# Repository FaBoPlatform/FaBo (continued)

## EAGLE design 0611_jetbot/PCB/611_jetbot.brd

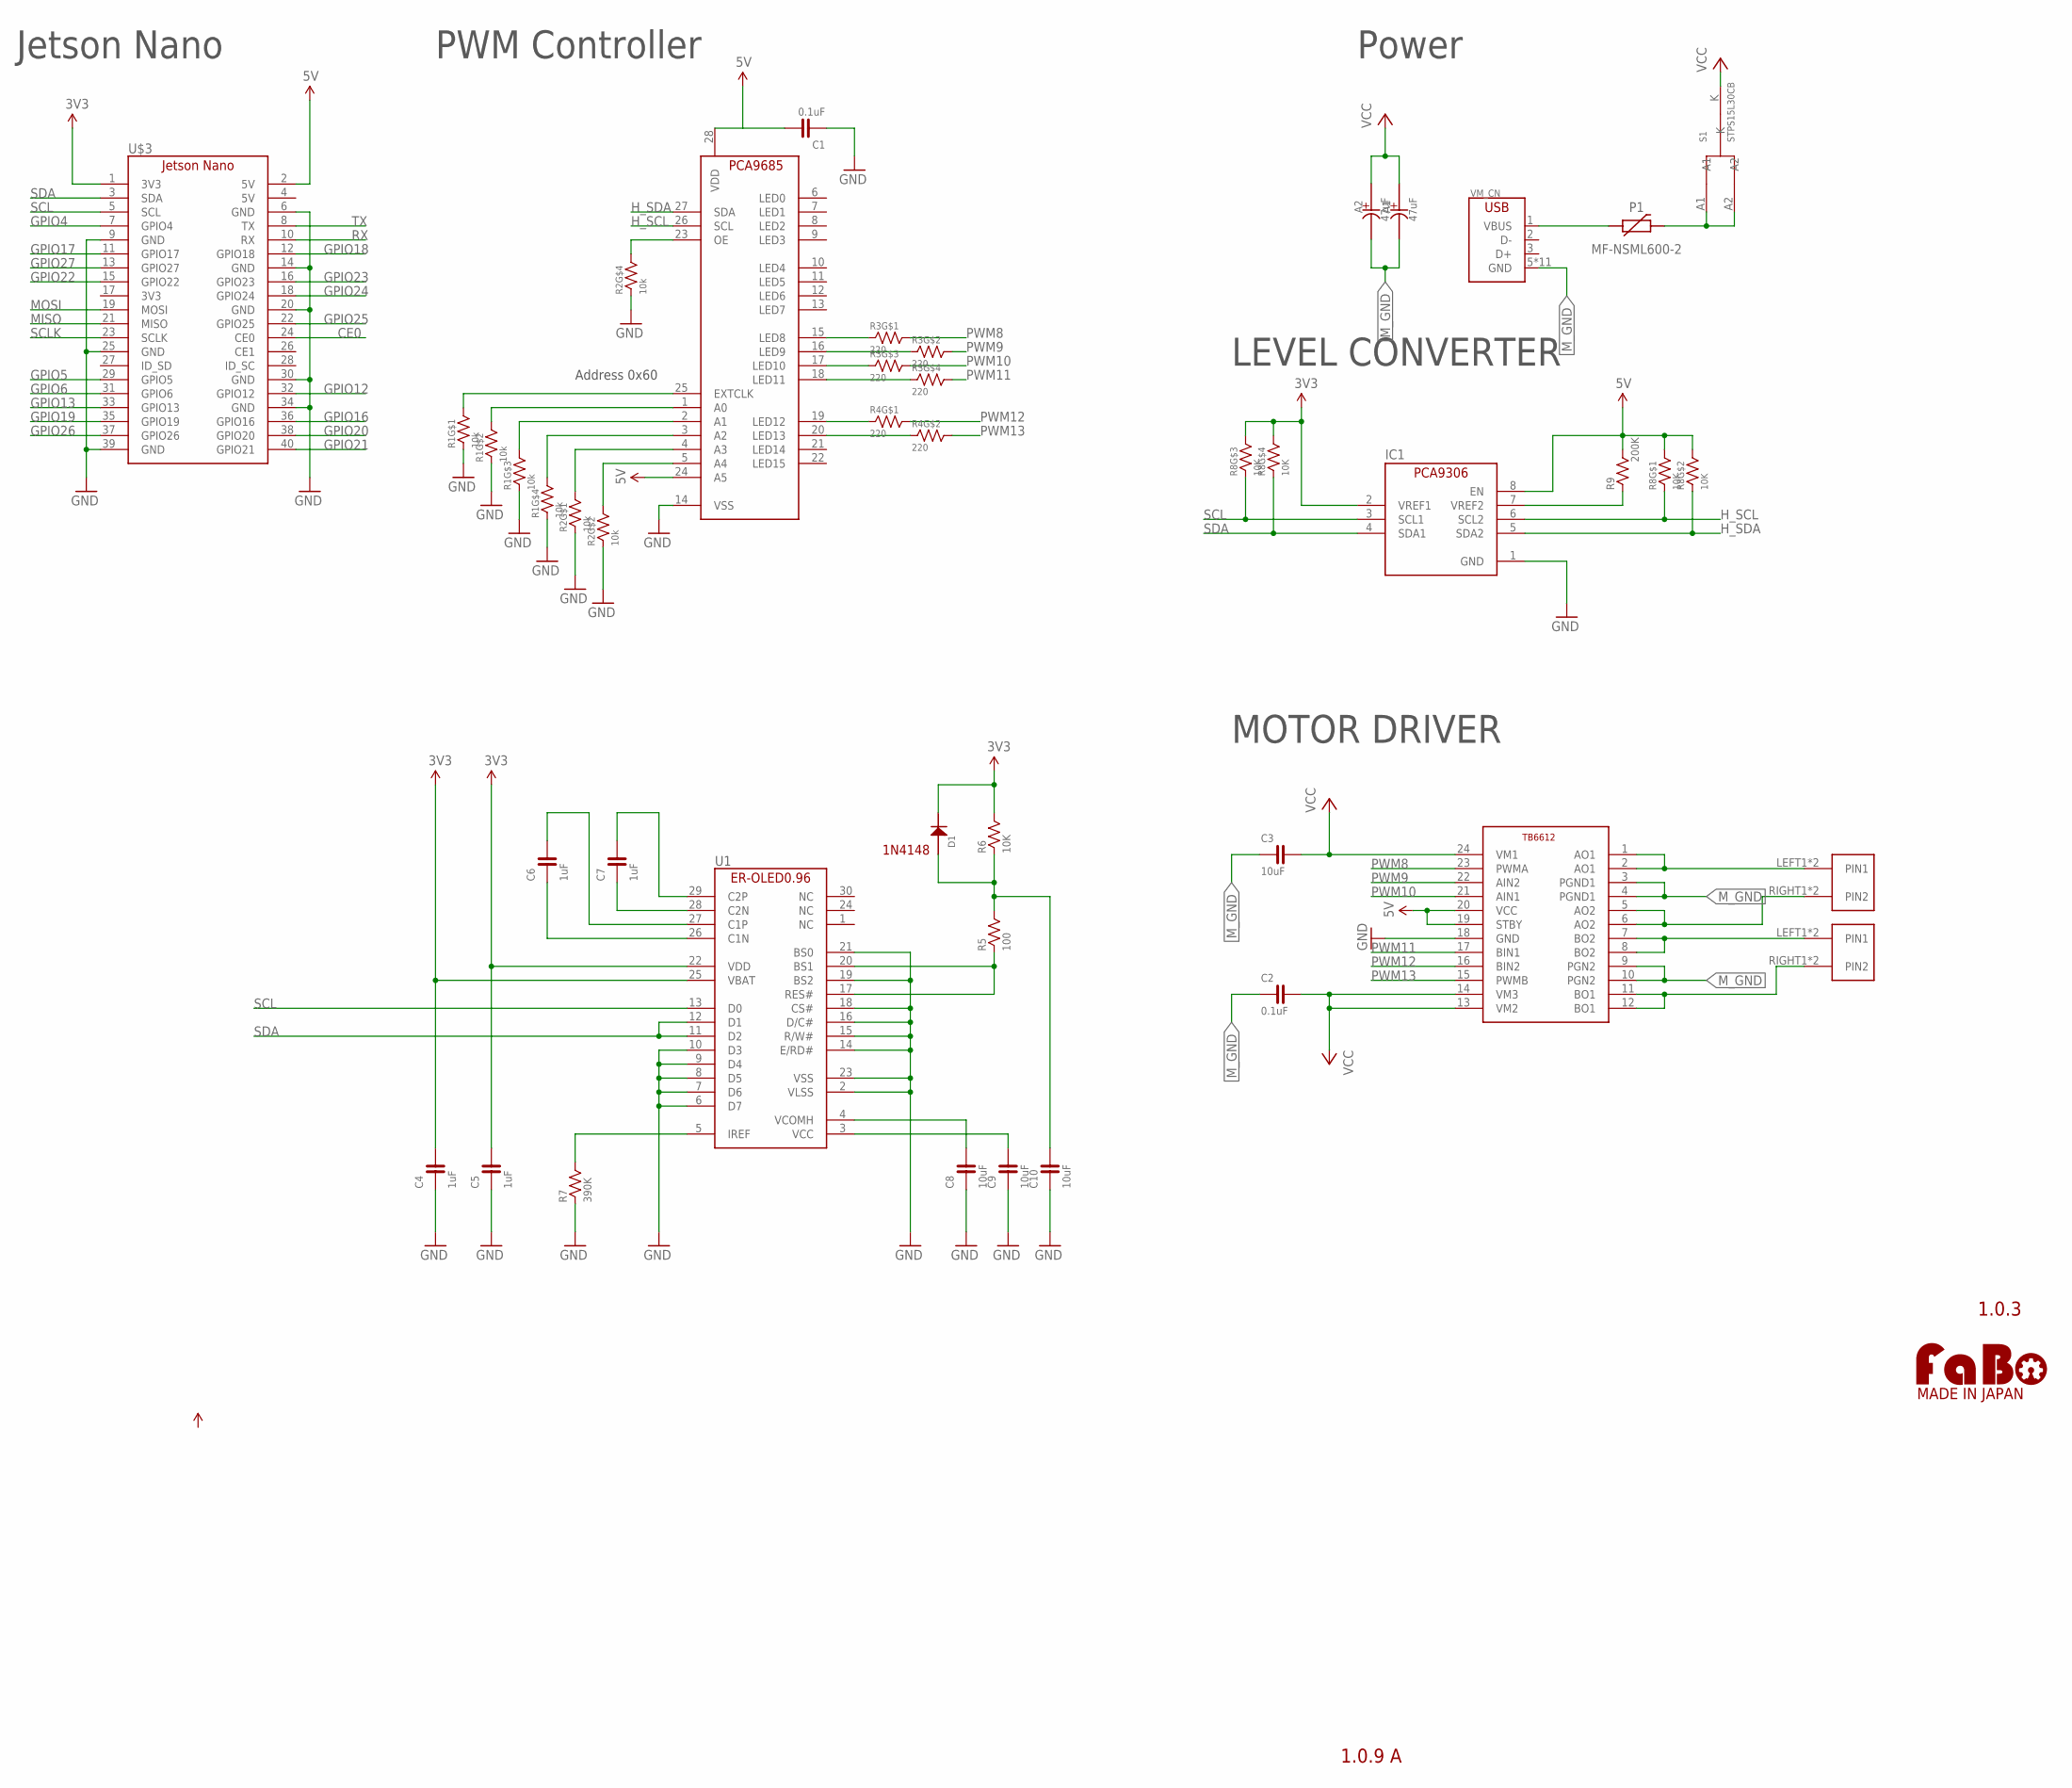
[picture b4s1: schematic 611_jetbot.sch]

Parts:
A1, A2: 47uF; D60
C1, C2: 0.1uF; 0603
C3: 10uF; 0603
C4, C5, C6, C7: 1uF; 0603-BOTTOM
C8, C9, C10: 10uF; 0603-BOTTOM
D1: 1N4148; 1N4148W
IC1: PCA9306_SSOP; 8PIN-SSOP
P1: MF-NSML600-2; 1206
R1, R2: 10k; EXBV8V
R3, R4: 220; EXBV8V
R5: 100; 0603-BOTTOM
R6: 10K; 0603-BOTTOM
R7: 390K; 0603-BOTTOM
R8: 10K; EXBV8V
R9: 200K; 0603
S1: STPS15L30CB; STPS15L30C
U1: ER-OLED0.96-1ER-CON30HT-1; ER-CON30HT-1
U$3: JETSON_NANO
U$5: TB6612
U$6, U$8: ML-1400-S1
U$9: PCA9685
U$14: LOGO_FABO-M; LOGO_FABO_MS
VM_CN: USB-ZX62D; ZX62D-B-5PA8

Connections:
3V3: C4.2, D1.CATHODE, IC1.2 (VREF1), R6.2, R8.5 (2), R8.6 (2), U1.25 (VBAT), U$3.1 (3V3), U$3.17 (3V3)
5V: C1.2, IC1.8 (EN), R8.7 (2), R8.8 (2), R9.2, U$3.2 (5V), U$5.19 (STBY), U$5.20 (VCC), U$9.24 (A5), U$9.28 (VDD)
CE0: U$3.24 (CE0)
GND: C1.1, C4.1, C5.1, C8.1, C9.1, C10.1, IC1.1 (GND), R1.1, R1.2 (1), R1.3 (1), R1.4 (1), R2.1, R2.2 (1), R2.4 (1), R7.1, U1.2 (VLSS), U1.6 (D7), U1.7 (D6), U1.8 (D5), U1.9 (D4), U1.10 (D3), U1.14 (E/RD#), U1.15 (R/W#), U1.16 (D/C#), U1.18 (CS#), U1.19 (BS2), U1.21 (BS0), U1.23 (VSS), U$3.6 (GND), U$3.9 (GND), U$3.14 (GND), U$3.20 (GND), U$3.25 (GND), U$3.30 (GND), U$3.34 (GND), U$3.39 (GND), U$5.18 (GND), U$9.14 (VSS)
GPIO4: U$3.7 (GPIO4)
GPIO5: U$3.29 (GPIO5)
GPIO6: U$3.31 (GPIO6)
GPIO12: U$3.32 (GPIO12)
GPIO13: U$3.33 (GPIO13)
GPIO16: U$3.36 (GPIO16)
GPIO17: U$3.11 (GPIO17)
GPIO18: U$3.12 (GPIO18)
GPIO19: U$3.35 (GPIO19)
GPIO20: U$3.38 (GPIO20)
GPIO21: U$3.40 (GPIO21)
GPIO22: U$3.15 (GPIO22)
GPIO23: U$3.16 (GPIO23)
GPIO24: U$3.18 (GPIO24)
GPIO25: U$3.22 (GPIO25)
GPIO26: U$3.37 (GPIO26)
GPIO27: U$3.13 (GPIO27)
H_SCL: IC1.6 (SCL2), R8.1, U$9.26 (SCL)
H_SDA: IC1.5 (SDA2), R8.2 (1), U$9.27 (SDA)
MISO: U$3.21 (MISO)
MOSI: U$3.19 (MOSI)
M_GND: A1.MINUS (-), A2.MINUS (-), C2.1, C3.1, U$5.3 (PGND1), U$5.4 (PGND1), U$5.9 (PGN2), U$5.10 (PGN2), VM_CN.5 (GND), VM_CN.B1 (GND), VM_CN.B2 (GND), VM_CN.B3 (GND), VM_CN.B4 (GND), VM_CN.T1 (GND), VM_CN.T2 (GND), VM_CN.T3 (GND), VM_CN.T4 (GND), VM_CN.T5 (GND), VM_CN.T6 (GND)
unnamed: R3.1, U$9.15 (LED8)
unnamed: R3.2 (1), U$9.16 (LED9)
unnamed: R3.3 (1), U$9.17 (LED10)
unnamed: R3.4 (1), U$9.18 (LED11)
unnamed: R4.1, U$9.19 (LED12)
unnamed: R2.5 (2), U$9.23 (OE)
unnamed: R1.8 (2), U$9.25 (EXTCLK)
unnamed: R1.7 (2), U$9.1 (A0)
unnamed: R1.6 (2), U$9.2 (A1)
unnamed: R1.5 (2), U$9.3 (A2)
unnamed: R2.8 (2), U$9.4 (A3)
unnamed: R2.7 (2), U$9.5 (A4)
unnamed: C6.2, U1.27 (C1P)
unnamed: R4.2 (1), U$9.20 (LED13)
unnamed: C6.1, U1.26 (C1N)
unnamed: U$5.1 (AO1), U$5.2 (AO1), U$6.LEFT1 (PIN1), U$6.LEFT2 (PIN1)
unnamed: U$5.5 (AO2), U$5.6 (AO2), U$6.RIGHT1 (PIN2), U$6.RIGHT2 (PIN2)
unnamed: C7.1, U1.28 (C2N)
unnamed: U$5.7 (BO2), U$5.8 (BO2), U$8.LEFT1 (PIN1), U$8.LEFT2 (PIN1)
unnamed: C7.2, U1.29 (C2P)
unnamed: U$5.11 (BO1), U$5.12 (BO1), U$8.RIGHT1 (PIN2), U$8.RIGHT2 (PIN2)
unnamed: R7.2, U1.5 (IREF)
unnamed: C8.2, U1.4 (VCOMH)
unnamed: C9.2, U1.3 (VCC)
unnamed: R5.1, U1.17 (RES#), U1.20 (BS1)
unnamed: C10.2, D1.ANODE, R5.2, R6.1
unnamed: C5.2, U1.22 (VDD)
unnamed: IC1.7 (VREF2), R9.1
PTCP1: P1.P$1 (1), VM_CN.1 (VBUS)
PTCP2: P1.P$2 (2), S1.A1, S1.A2
PWM8: R3.8 (2), U$5.23 (PWMA)
PWM9: R3.7 (2), U$5.22 (AIN2)
PWM10: R3.6 (2), U$5.21 (AIN1)
PWM11: R3.5 (2), U$5.17 (BIN1)
PWM12: R4.8 (2), U$5.16 (BIN2)
PWM13: R4.7 (2), U$5.15 (PWMB)
RX: U$3.10 (RX)
SCL: IC1.3 (SCL1), R8.3 (1), U1.13 (D0), U$3.5 (SCL)
SCLK: U$3.23 (SCLK)
SDA: IC1.4 (SDA1), R8.4 (1), U1.11 (D2), U1.12 (D1), U$3.3 (SDA)
TX: U$3.8 (TX)
VCC: A1.PLUS (+), A2.PLUS (+), C2.2, C3.2, S1.K, U$5.13 (VM2), U$5.14 (VM3), U$5.24 (VM1)

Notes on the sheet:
1.0.3
Jetson Nano
PWM Controller
Power
MOTOR DRIVER
Address 0x60
1.0.9 A
1N4148
LEVEL CONVERTER

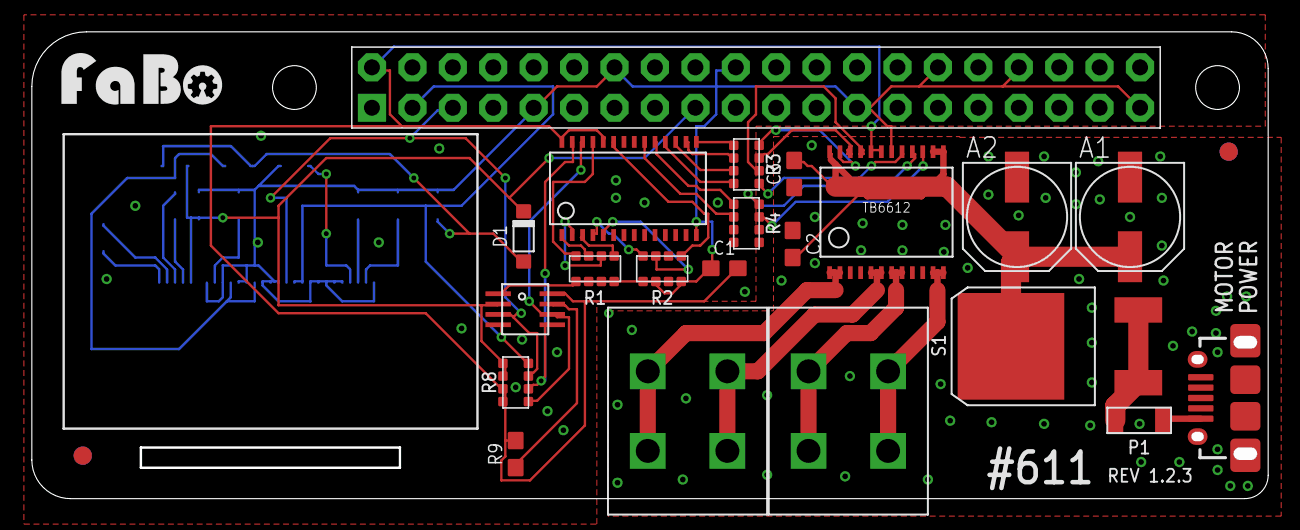
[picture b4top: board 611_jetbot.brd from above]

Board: 2 copper layers, 77.7 x 29.3 mm, 37 parts (0 on the bottom side), 45 nets.

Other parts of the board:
U$2, U$4: MARK_POINT_3MM
U$7, U$10: MARK_POINT_3MM_BOTTOM

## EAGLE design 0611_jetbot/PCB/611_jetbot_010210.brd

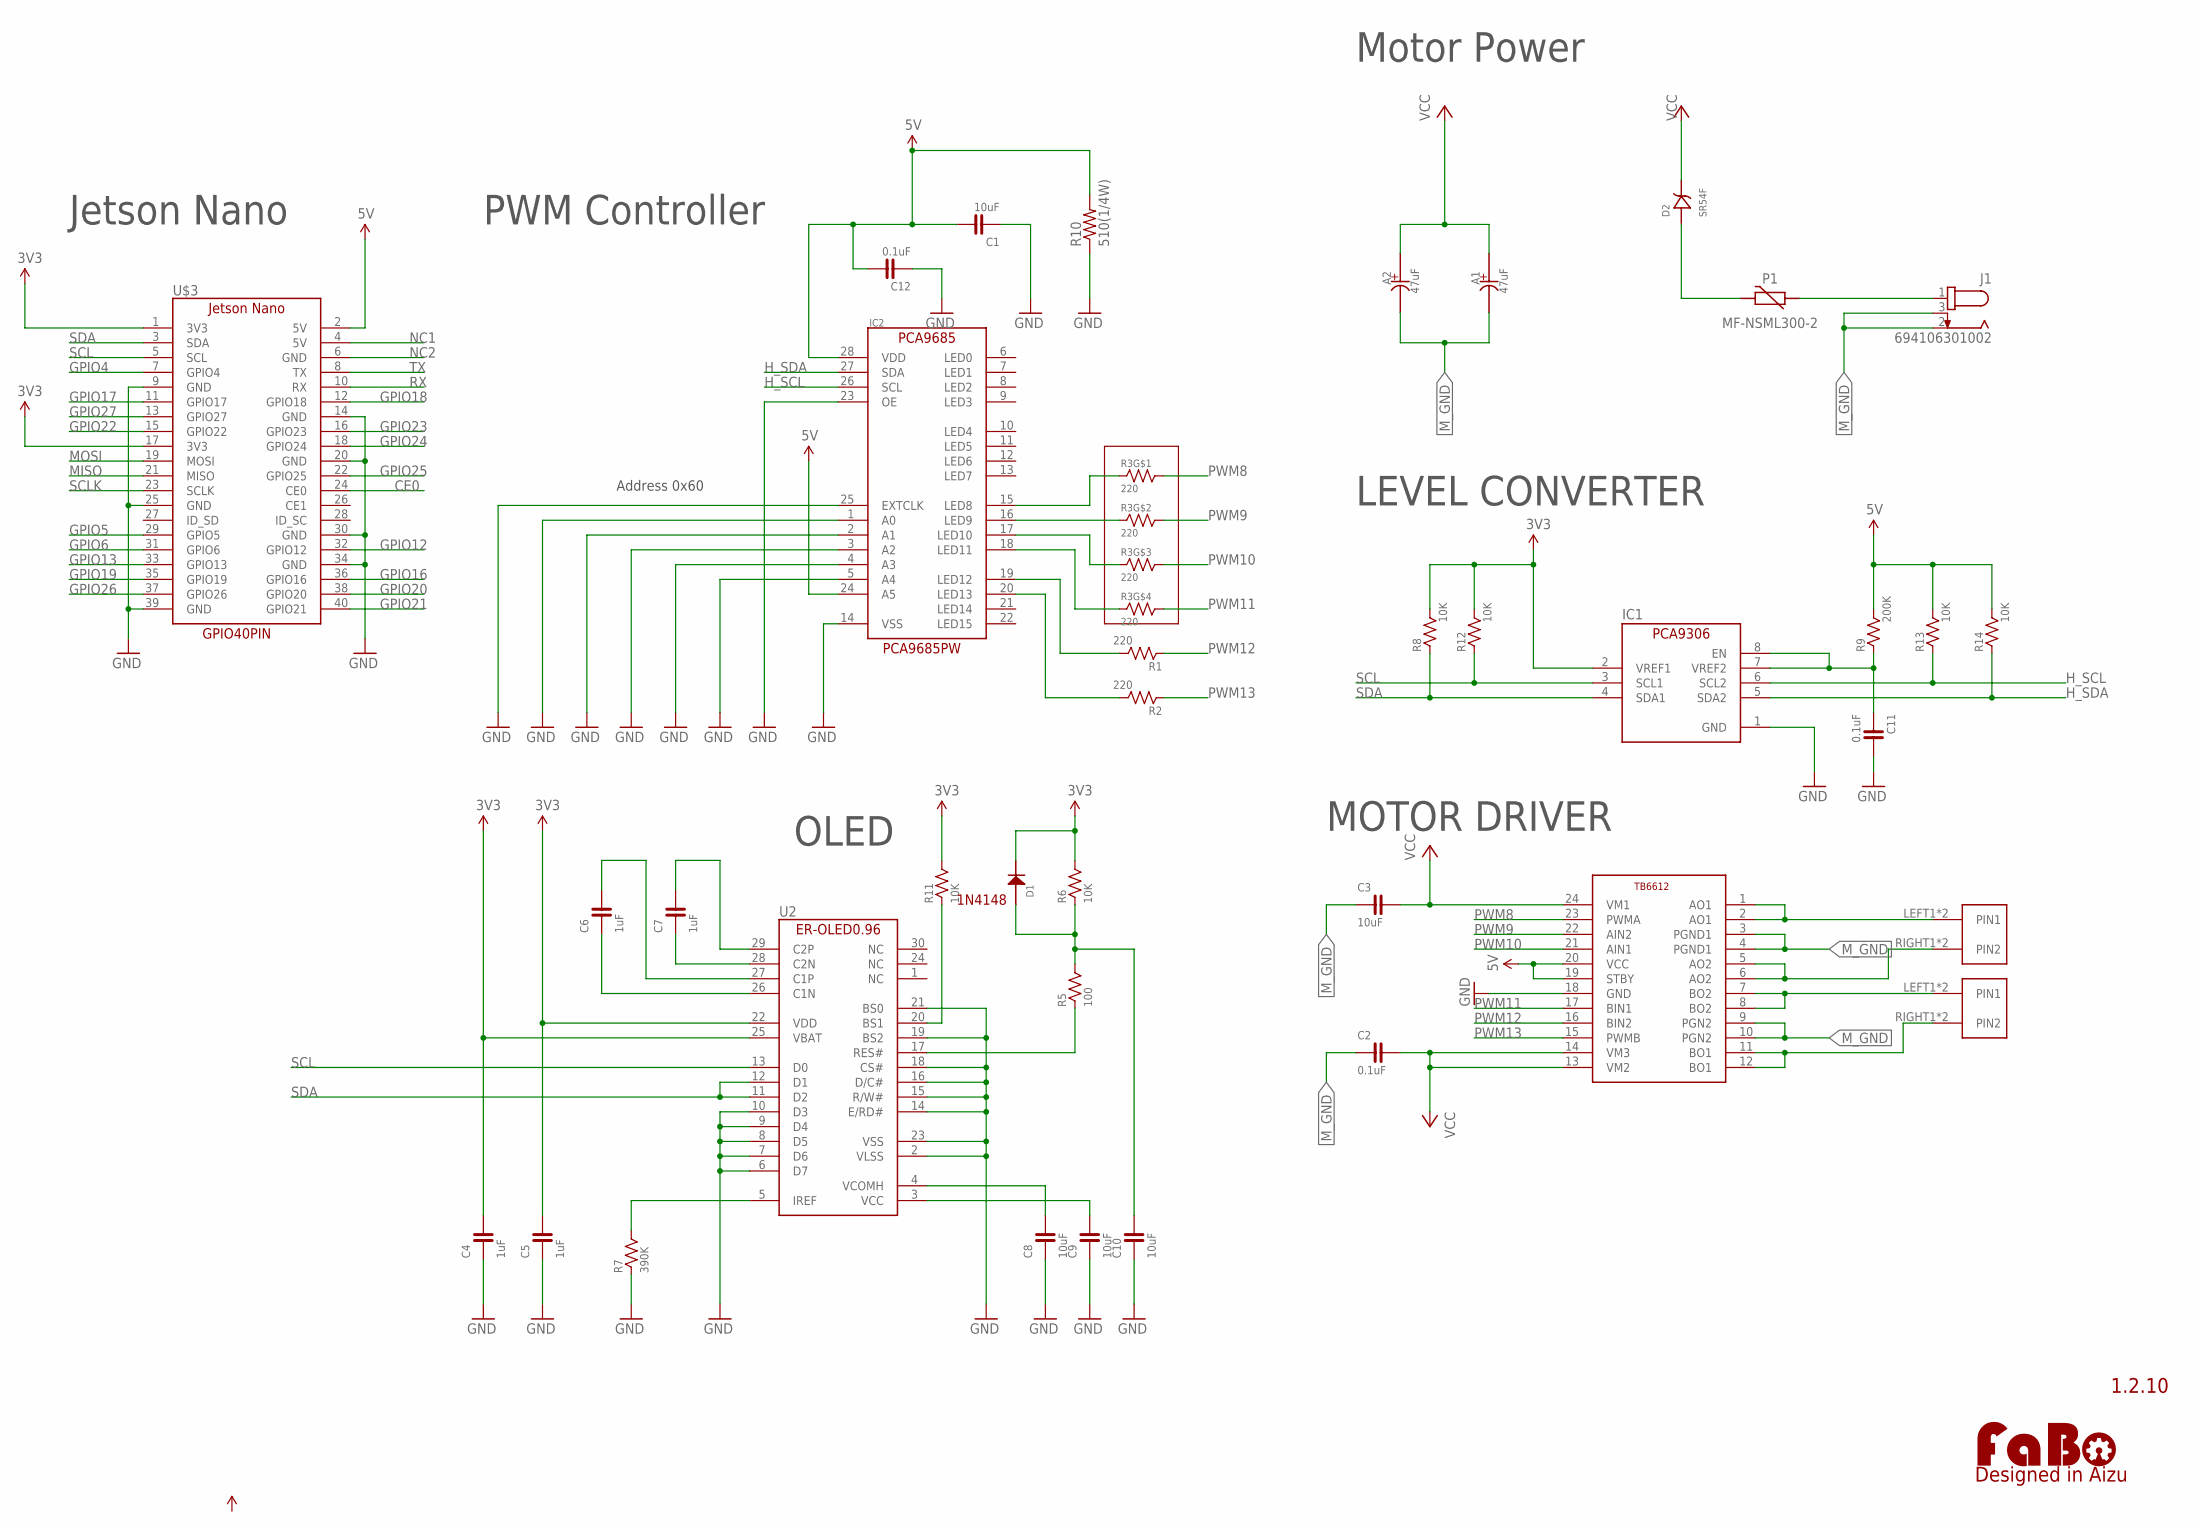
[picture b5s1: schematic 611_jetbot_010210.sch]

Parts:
A1, A2: 47uF; D60
C1, C3: 10uF; 0603
C2, C11, C12: 0.1uF; 0603
C4, C5, C6, C7: 1uF; 0603-BOTTOM
C8, C9, C10: 10uF; 0603-BOTTOM
D1: 1N4148; 1N4148W
D2: SR54F; SMBF
IC1: PCA9306_SSOP; 8PIN-SSOP
IC2: PCA9685PW,BS; PCA9685
J1: 694106301002
LOGO1: LOGO_FABO-M; LOGO_FABO_M
P1: MF-NSML300-2; 1206
R1, R2: 220; 0603
R3: 220; EXBV8V
R5: 100; 0603-BOTTOM
R6, R11: 10K; 0603-BOTTOM
R7: 390K; 0603-BOTTOM
R8, R12, R13, R14: 10K; 0603
R9: 200K; 0603
R10: 510(1/4W); R0805
U2: ER-OLED0.96-1ER-CON30HT-1_REV2; ER-CON30HT-1_REV2
U$3: JETSON_NANO
U$5: TB6612
U$6, U$8: ML-1400-S1

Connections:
3V3: C4.2, C5.2, D1.CATHODE, IC1.2 (VREF1), R6.2, R8.2, R11.2, R12.2, U2.22 (VDD), U2.25 (VBAT), U$3.1 (3V3), U$3.17 (3V3)
5V: C1.2, C12.2, IC2.24 (A5), IC2.28 (VDD), R9.2, R10.2, R13.2, R14.2, U$3.2 (5V), U$5.19 (STBY), U$5.20 (VCC)
CE0: U$3.24 (CE0)
GND: C1.1, C4.1, C5.1, C8.1, C9.1, C10.1, C11.2, C12.1, IC1.1 (GND), IC2.1 (A0), IC2.2 (A1), IC2.3 (A2), IC2.4 (A3), IC2.5 (A4), IC2.14 (VSS), IC2.23 (OE), IC2.25 (EXTCLK), R7.1, R10.1, U2.2 (VLSS), U2.6 (D7), U2.7 (D6), U2.8 (D5), U2.9 (D4), U2.10 (D3), U2.14 (E/RD#), U2.15 (R/W#), U2.16 (D/C#), U2.18 (CS#), U2.19 (BS2), U2.21 (BS0), U2.23 (VSS), U$3.9 (GND), U$3.14 (GND), U$3.20 (GND), U$3.25 (GND), U$3.30 (GND), U$3.34 (GND), U$3.39 (GND), U$5.18 (GND)
GPIO4: U$3.7 (GPIO4)
GPIO5: U$3.29 (GPIO5)
GPIO6: U$3.31 (GPIO6)
GPIO12: U$3.32 (GPIO12)
GPIO13: U$3.33 (GPIO13)
GPIO16: U$3.36 (GPIO16)
GPIO17: U$3.11 (GPIO17)
GPIO18: U$3.12 (GPIO18)
GPIO19: U$3.35 (GPIO19)
GPIO20: U$3.38 (GPIO20)
GPIO21: U$3.40 (GPIO21)
GPIO22: U$3.15 (GPIO22)
GPIO23: U$3.16 (GPIO23)
GPIO24: U$3.18 (GPIO24)
GPIO25: U$3.22 (GPIO25)
GPIO26: U$3.37 (GPIO26)
GPIO27: U$3.13 (GPIO27)
H_SCL: IC1.6 (SCL2), IC2.26 (SCL), R13.1
H_SDA: IC1.5 (SDA2), IC2.27 (SDA), R14.1
MISO: U$3.21 (MISO)
MOSI: U$3.19 (MOSI)
M_GND: A1.MINUS (-), A2.MINUS (-), C2.1, C3.1, J1.2, J1.3, U$5.3 (PGND1), U$5.4 (PGND1), U$5.9 (PGN2), U$5.10 (PGN2)
unnamed: C6.2, U2.27 (C1P)
unnamed: C6.1, U2.26 (C1N)
unnamed: U$5.1 (AO1), U$5.2 (AO1), U$6.LEFT1 (PIN1), U$6.LEFT2 (PIN1)
unnamed: U$5.5 (AO2), U$5.6 (AO2), U$6.RIGHT1 (PIN2), U$6.RIGHT2 (PIN2)
unnamed: C7.1, U2.28 (C2N)
unnamed: U$5.7 (BO2), U$5.8 (BO2), U$8.LEFT1 (PIN1), U$8.LEFT2 (PIN1)
unnamed: C7.2, U2.29 (C2P)
unnamed: U$5.11 (BO1), U$5.12 (BO1), U$8.RIGHT1 (PIN2), U$8.RIGHT2 (PIN2)
unnamed: R7.2, U2.5 (IREF)
unnamed: C8.2, U2.4 (VCOMH)
unnamed: C9.2, U2.3 (VCC)
unnamed: R5.1, U2.17 (RES#)
unnamed: C10.2, D1.ANODE, R5.2, R6.1
unnamed: R11.1, U2.20 (BS1)
unnamed: C11.1, IC1.7 (VREF2), IC1.8 (EN), R9.1
NC1: U$3.4 (5V)
NC2: U$3.6 (GND)
P8: IC2.15 (LED8), R3.1
P9: IC2.16 (LED9), R3.2 (1)
P10: IC2.17 (LED10), R3.3 (1)
P11: IC2.18 (LED11), R3.4 (1)
P12: IC2.19 (LED12), R1.2
P13: IC2.20 (LED13), R2.2
PTCP1: J1.1, P1.1
PTCP2: D2.ANODE, P1.2
PWM8: R3.8 (2), U$5.23 (PWMA)
PWM9: R3.7 (2), U$5.22 (AIN2)
PWM10: R3.6 (2), U$5.21 (AIN1)
PWM11: R3.5 (2), U$5.17 (BIN1)
PWM12: R1.1, U$5.16 (BIN2)
PWM13: R2.1, U$5.15 (PWMB)
RX: U$3.10 (RX)
SCL: IC1.3 (SCL1), R12.1, U2.13 (D0), U$3.5 (SCL)
SCLK: U$3.23 (SCLK)
SDA: IC1.4 (SDA1), R8.1, U2.11 (D2), U2.12 (D1), U$3.3 (SDA)
TX: U$3.8 (TX)
VCC: A1.PLUS (+), A2.PLUS (+), C2.2, C3.2, D2.CATHODE, U$5.13 (VM2), U$5.14 (VM3), U$5.24 (VM1)

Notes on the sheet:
1.2.10
Jetson Nano
PWM Controller
MOTOR DRIVER
Address 0x60
1N4148
LEVEL CONVERTER
OLED
Motor Power
GPIO40PIN
PCA9685PW

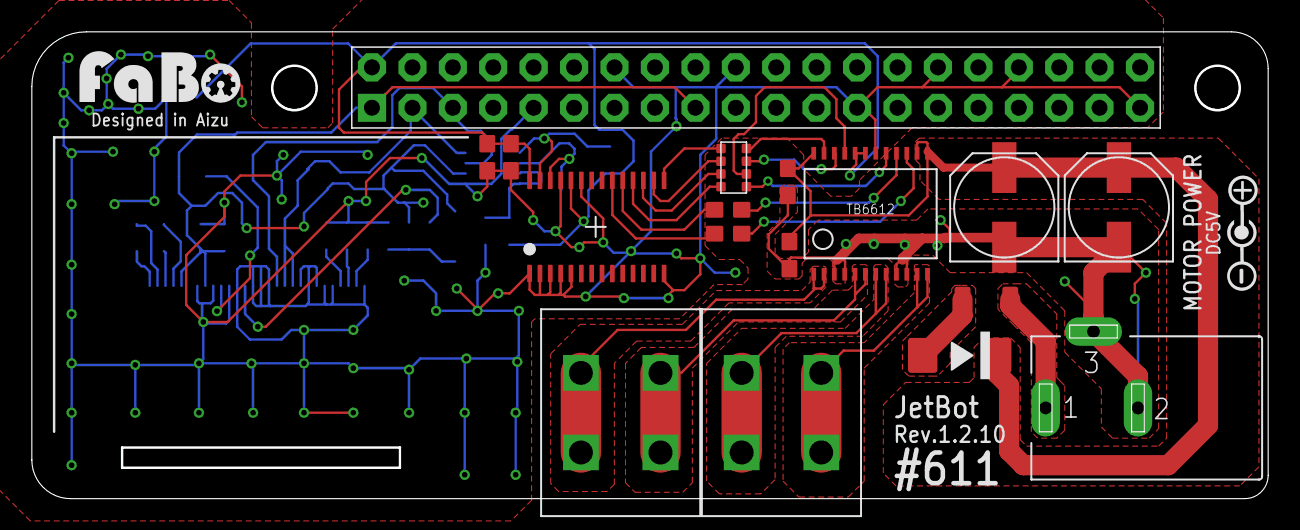
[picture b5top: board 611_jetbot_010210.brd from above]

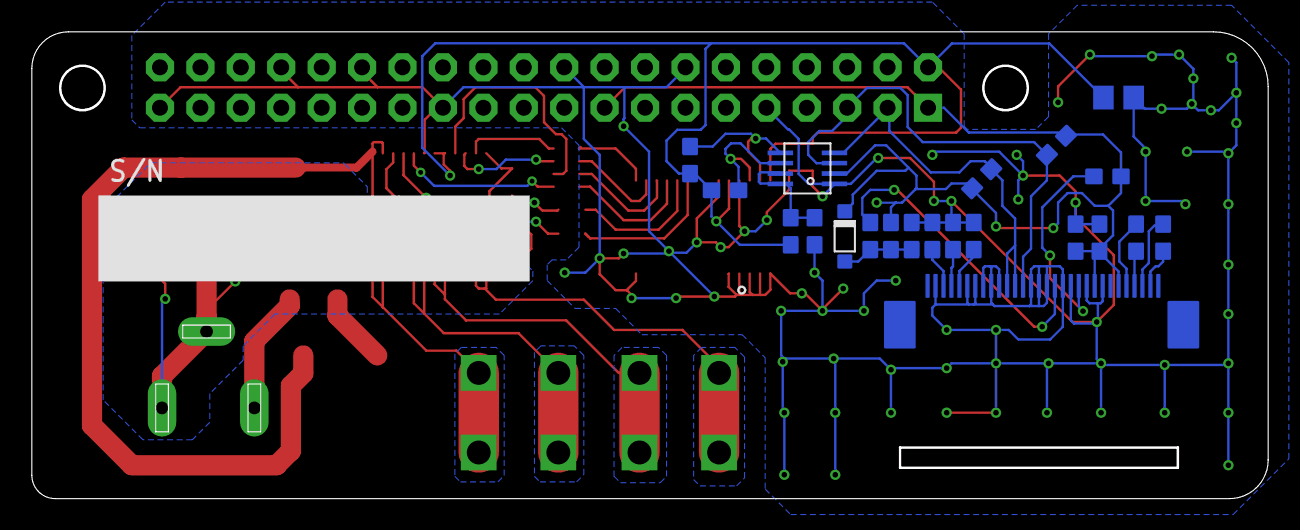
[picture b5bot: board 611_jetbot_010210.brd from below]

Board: 2 copper layers, 77.7 x 29.3 mm, 39 parts (9 on the bottom side), 38 nets.
